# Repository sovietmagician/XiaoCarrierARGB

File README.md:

# XiaoCarrierARGB

Adressable RGB carrier board for Seeed Xiao Esp32 modules, deisgned for c6 or s3 variants. Input voltage designed to be 12-24V and has an back current protection mechanism to allow the Xiao to be connected to a pc while the board is powered from elsewhere. 
- NOTE the 5v level shifters needed for the RGB data signalling are only powered from the 12-24v input and only connecting the xiao to power will not allow for RGB strip control. 
---
## Features

- 3 Dedicated 5V levelshifted outputs for LED strip data lines
- 8 GPIO breakouts capable of all features the selected Xiao is capable of including
  - SPI
  - I2C
  - Analog inputs
  - UART
- optional pull up/down resistors for GPIO breakouts can be pulled to:
  - 5V
  - 3.3V
  - GND
- 1.5 Amps of 5V output
- 1 Amp of 3.3V output

---

## USER INFO

### BoM
[Interactive Bill of Materials](https://sovietmagician.github.io/XiaoCarrierARGB/bom/ibom.html "IBOM")
Component Manufacturer Part Numbers are included for ICs and certain passives with critical values. In addition Digikey and LCSC(chinese) part distributor numbers are included in the BoM as well. The part numbers for passives have been left blank as an excercise for the reader. Note for C2 C3 C8, __these capacitors must be rated to 30V at a minimum__.
### Notes about componet placement/population
The following components are NOT OPTIONAL
- C2 C3 C5 C6 C7
  - These capacitors are necessary for the operation of the buck converter a provisional value of 22µF was selected but it is possible more may be necessary
- C5
  - Bootstrap capacitor should be 100nF

- L1
  - The main inductor for the buck converter without it it just wont function at all
- D1
  - Needed to allow the Xiao to be both plugged in to a computer and have its primary input voltage connected
- U2
  - The buck converter IC without it it will not accept 12-24V input and the level shifters will not be able to drive the RGB data lines
- R1 R2
  - Feedback resistors to allow the buck to actually regulate to the correct (5) Voltage. These must be populated at the right values in the right spots, R1-110kΩ R2-15kΩ

The following components are highly recommended
- U1 
  - The LDO for the 3.3V pins on the GPIO breakout, while not STRICTLY necessary it is highly recommended 
- C1 C4
  - These 1µF capacitors are necessary for 3.3V LDO functionality to supply power to the power pins accompanying the GPIO breakouts A higher value may be used but the total capacitance on this line MAY NOT exceed 10µF to keep the Xiao's VBUS pin inline with USB spec
- F1
  - Input protection to prevent the board from drawing too much current, should save the board in the event of shorts or overcurrent events
- U4 U5 U6
  - these are the level shifters to drive the LED strips, not all need to be populated but populating none is kind of silly 
- C8
  - A good decoupling cap of 100nF is nice to have and since the previous 100nF cap is necessary theres no real reason not to populate it 
  
The following are strictly optional
- R3-R10
  - these are pull up/down resistors meant to allow for ease of use of the GPIO breakouts some communication busses need pull ups or pull downs and its just usecase dependant
- R11-13
  - these are series resistors meant to minimize reflections in the even of exceptionally long data line runs(ie there is a very long wire between the board and the first IC on the LED strip) can be subbed for 0Ω resistors or pads can be bridged with solder or wire

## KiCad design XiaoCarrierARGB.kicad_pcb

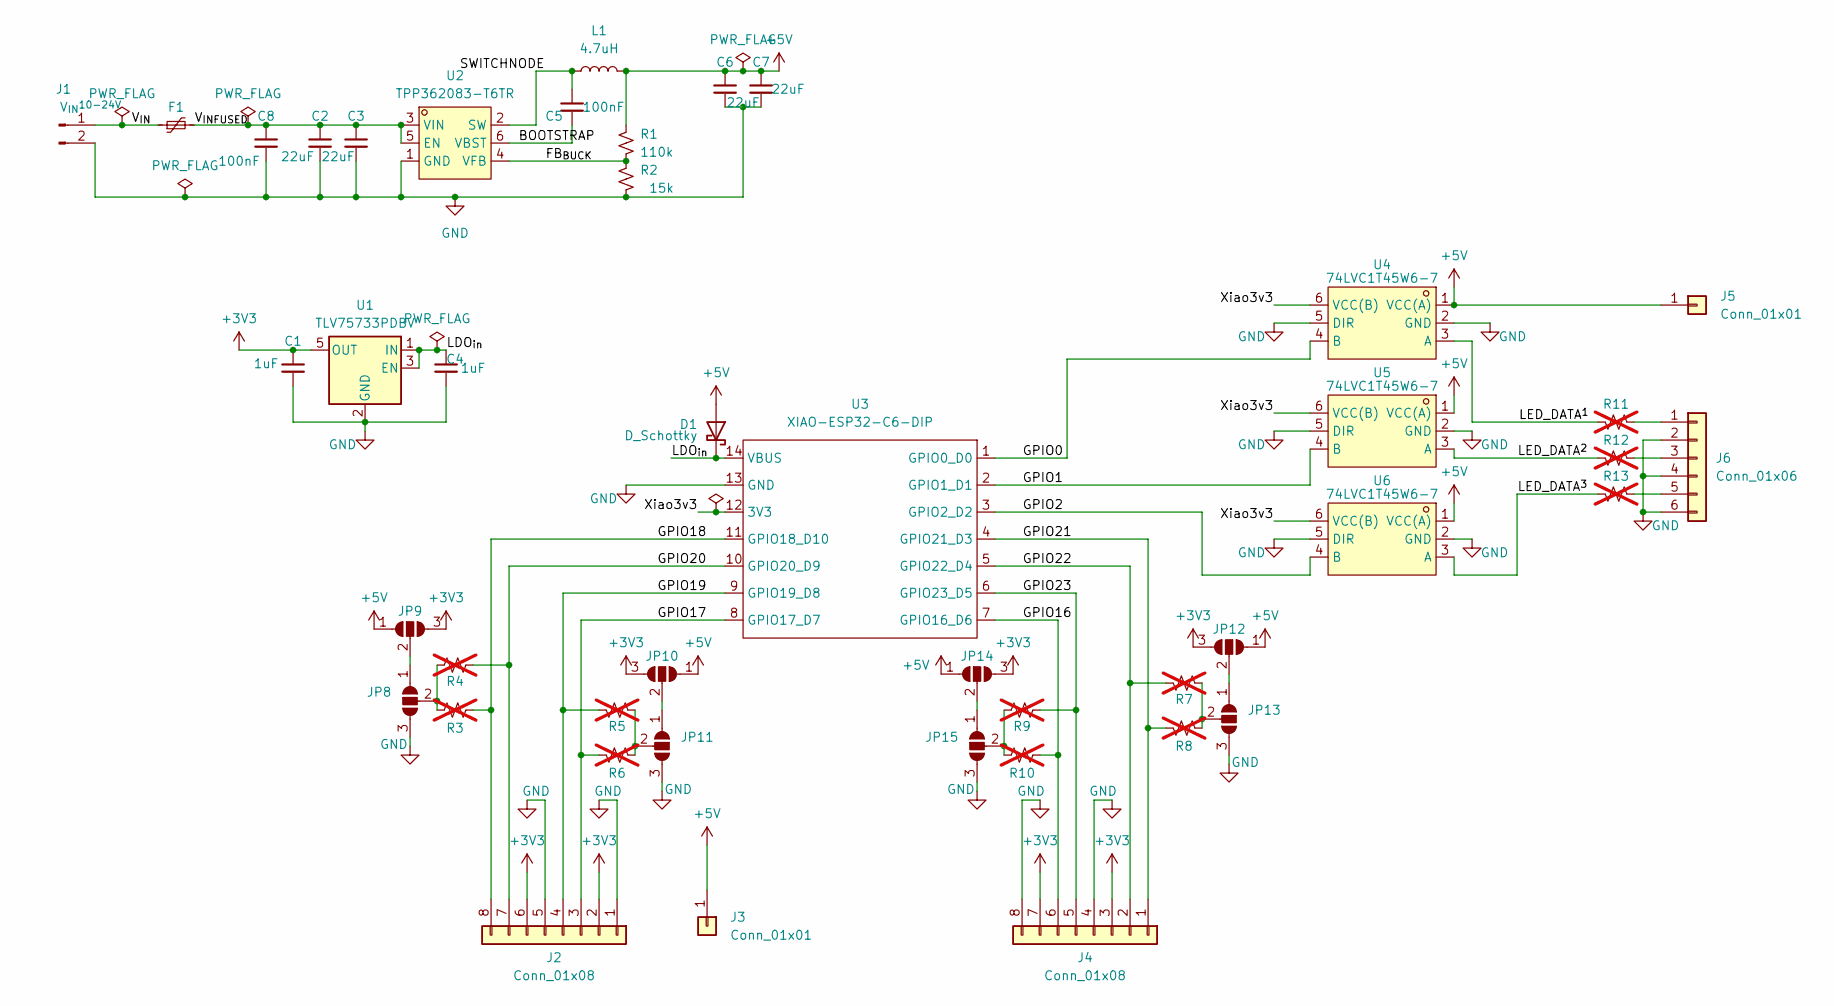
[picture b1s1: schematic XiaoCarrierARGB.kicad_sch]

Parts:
C1, C4: 1uF; C_0805_2012Metric_Pad1.18x1.45mm_HandSolder
C2, C3, C6, C7: 22uF; C_0805_2012Metric_Pad1.18x1.45mm_HandSolder
C5, C8: 100nF; C_0805_2012Metric_Pad1.18x1.45mm_HandSolder
D1: D_Schottky; D_SMA; MPN SBA520AFC_R1_00001; DigiKey Part 3757-SBA520AFC_R1_00001
F1: YAGEO SMD1812B110TF/33; Fuse_1812_4532Metric; LCSC Part C269134
J1: V_{IN}^{10-24V}; PinHeader_1x02_P2.54mm_Vertical
J2, J4: Conn_01x08; PinHeader_1x08_P2.54mm_Vertical
J3, J5: Conn_01x01; PinHeader_1x01_P2.54mm_Vertical
J6: Conn_01x06; PinHeader_1x06_P2.54mm_Vertical
JP8, JP9, JP10, JP11, JP12, JP13, JP14, JP15: SolderJumper_3_Open; SolderJumper-3_P1.3mm_Open_Pad1.0x1.5mm
L1: 4.7uH; L_Chilisin_BWVS00606045; MPN IFSC2020DEER4R7M01; DigiKey Part 541-IFSC2020DEER4R7M01CT-ND
R1: 110k; R_0805_2012Metric
R2: 15k; R_0805_2012Metric
R3, R4, R5, R6, R7, R8, R9, R10, R11, R12, R13: R_Small_US; R_0805_2012Metric; not fitted
U1: TLV75733PDBV; SOT-23-5; MPN TLV75733PDBVR; DigiKey Part 296-50414
U2: TPP362083-T6TR; TSOT-23-6; MPN TPP362081-T6TR; LCSC Part C29073195
U3: XIAO-ESP32-C6-DIP
U4, U5, U6: 74LVC1T45W6-7; SOT-23-6; MPN 74LVC1T45W6-7; LCSC Part C168856

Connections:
+3V3: C1.1, J2.2, J2.6, J4.3, J4.7, JP9.3 (B), JP10.3 (B), JP12.3 (B), JP14.3 (B), U1.5 (OUT)
+5V: C6.1, C7.1, D1.2 (A), J3.1 (Pin_1_1), J5.1 (Pin_1_1), JP9.1 (A), JP10.1 (A), JP12.1 (A), JP14.1 (A), L1.2, R1.1, U4.1 (VCC(A)), U5.1 (VCC(A)), U6.1 (VCC(A))
/BOOTSTRAP: C5.1, U2.6 (VBST)
/FB_{BUCK}: R1.2, R2.1, U2.4 (VFB)
/GPIO0: U3.1 (GPIO0_D0), U4.4 (B)
/GPIO1: U3.2 (GPIO1_D1), U5.4 (B)
/GPIO2: U3.3 (GPIO2_D2), U6.4 (B)
/GPIO16: J4.6, R10.2, U3.7 (GPIO16_D6)
/GPIO17: J2.3, R6.2, U3.8 (GPIO17_D7)
/GPIO18: J2.8, R3.2, U3.11 (GPIO18_D10)
/GPIO19: J2.4, R5.2, U3.9 (GPIO19_D8)
/GPIO20: J2.7, R4.2, U3.10 (GPIO20_D9)
/GPIO21: J4.1, R8.2, U3.4 (GPIO21_D3)
/GPIO22: J4.2, R7.2, U3.5 (GPIO22_D4)
/GPIO23: J4.5, R9.2, U3.6 (GPIO23_D5)
/LDO_{in}: C4.1, D1.1 (K), U1.1 (IN), U1.3 (EN), U3.14 (VBUS)
/LED_DATA^{1}: R11.2, U4.3 (A)
/LED_DATA^{2}: R12.2, U5.3 (A)
/LED_DATA^{3}: R13.2, U6.3 (A)
/SWITCHNODE: C5.2, L1.1, U2.2 (SW)
/V_{IN}: F1.1, J1.1
/V_{IN}_{FUSED}: C2.1, C3.1, C8.2, F1.2, U2.3 (VIN), U2.5 (EN)
/Xiao3v3: U3.12 (3V3), U4.6 (VCC(B)), U5.6 (VCC(B)), U6.6 (VCC(B))
GND: C1.2, C2.2, C3.2, C4.2, C6.2, C7.2, C8.1, J1.2, J2.1, J2.5, J4.4, J4.8, J6.2, J6.4, J6.6, JP8.3 (B), JP11.3 (B), JP13.3 (B), JP15.3 (B), R2.2, U1.2 (GND), U2.1 (GND), U3.13 (GND), U4.2 (GND), U4.5 (DIR), U5.2 (GND), U5.5 (DIR), U6.2 (GND), U6.5 (DIR)
unnamed: J6.1, R11.1
unnamed: J6.3, R12.1
unnamed: J6.5, R13.1
unnamed: JP8.1 (A), JP9.2 (C)
unnamed: JP8.2 (C), R3.1, R4.1
unnamed: JP10.2 (C), JP11.1 (A)
unnamed: JP11.2 (C), R5.1, R6.1
unnamed: JP12.2 (C), JP13.1 (A)
unnamed: JP13.2 (C), R7.1, R8.1
unnamed: JP14.2 (C), JP15.1 (A)
unnamed: JP15.2 (C), R9.1, R10.1

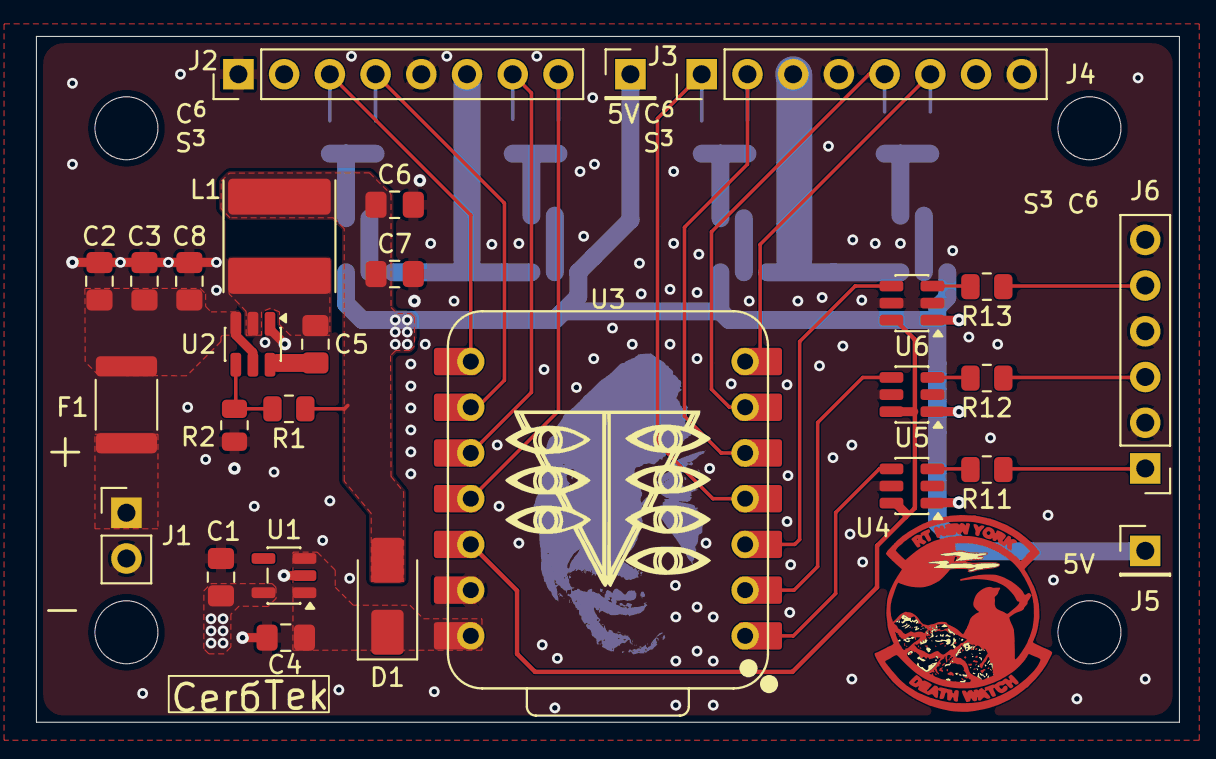
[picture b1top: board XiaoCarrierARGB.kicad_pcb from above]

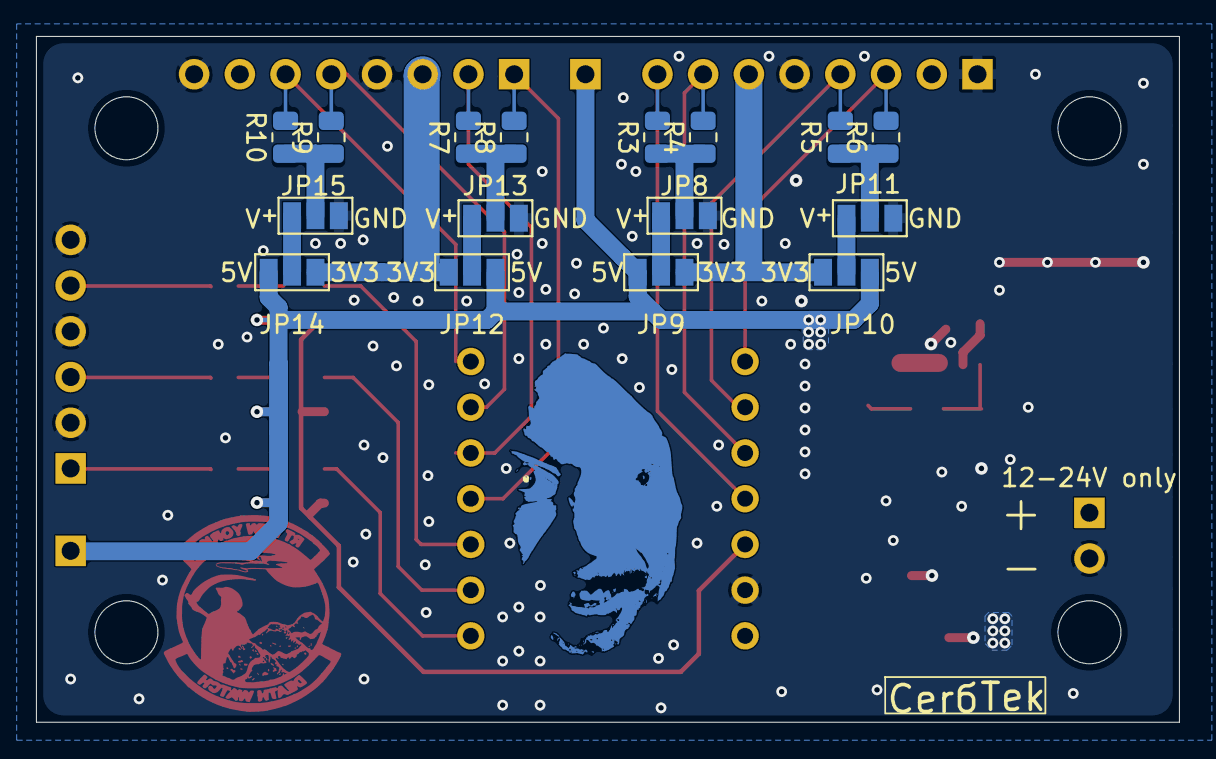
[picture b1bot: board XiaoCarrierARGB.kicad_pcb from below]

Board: 4 copper layers, 63.5 x 38.1 mm, 45 parts (16 on the bottom side), 35 nets.

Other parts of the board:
RT**: RT-NY; RT-NY-Patch
